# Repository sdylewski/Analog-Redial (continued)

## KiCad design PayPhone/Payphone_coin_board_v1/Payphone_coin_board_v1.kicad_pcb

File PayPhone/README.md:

# Payphone with Analog Redial

**In progress.** The Payphone tab is written and the coin board is released for fab, but
nothing here has run on a real payphone yet: no coin board has been built, and the firmware
has only run against simulated chips.

Analog Redial can run a real coin payphone: the handset lifts, a spoken message asks for
coins, the coin switches (or the line's coin tones) add up the credit, and the board
collects or returns the coins by firing the phone's coin relay. The project's first phone is
a GTE / Quadrum 120B style set.

| Doc | Covers |
|---|---|
| This one | the project as a whole: what the pieces are, status, payphone types, links |
| [coin-board.md](coin-board.md) | the coin board: how it works, output stage wiring pin by pin, parts and PCB layout |
| [payphone-firmware.md](payphone-firmware.md) | the firmware: the Payphone tab (coin tones, coin required, messages, log) and the coin board's driver |

Public version of the board reference: [docs/hardware-coin-board.md](../docs/hardware-coin-board.md).

## The pieces

- **Main board:** any Analog Redial board for the Payphone tab (coin required, messages,
  coin tones, the coin counter). The coin board plugs into v6's J11 I²C header.
- **Coin board** (`Payphone_coin_board_v1/`): makes up to 119 V to fire the coin relay in
  either direction, reads the 5 / 10 / 25 cent switches, and talks I²C. Released for fab,
  untested.
- **Instruction cards** (`instruction_cards/`): the printed cards for the phone's
  upper and lower panels, and their standard sizes (see its README).
- **Firmware** (`firmware/components/payphone/`, `coinboard/`): see
  [payphone-firmware.md](payphone-firmware.md).

## Payphone types

Payphones differ in how they report coins and how their coin relay is driven. These tables
collect what each known phone needs, one row per phone, so the firmware can later offer a
phone type to pick instead of setting each value by hand. Until then, the values in the
last table are the ones to set on the Payphone tab and on the coin board's jumpers.

To add a phone, add a row to each table, mark anything not measured **[verify]**, and note
in the last column where the numbers came from.

### 1. Identification

| Phone | Housing | Controller board | Made | Source |
|---|---|---|---|---|
| **GTE / Quadrum 120B style** (the project's first phone) | GTE / Quadrum, coin return lower right | **HB-1301-B** (40-pin DIP, two CP Clare reed relays, 310 V gas tube); smart or dumb not known **[verify]** | week 51, 1997 | photos and bench tests, 2026-10-24 to 2026-10-31 |

### 2. Coin detection

| Phone | Sensor | Cable | Wires | Signal | Coins | Coin tones |
|---|---|---|---|---|---|---|
| GTE / Quadrum 120B style | passive coin switches (measured) | 4-wire, Molex KK 396 (coin board J3) | green common; white quarter, red dime, blue nickel | contact to common, closes briefly per coin | 5, 10, 25 cents | not checked **[verify]** |

### 3. Coin relay

| Phone | Relay | Coils | Wires | Resistance | Operates at | Direction | Switch-off | Cable |
|---|---|---|---|---|---|---|---|---|
| GTE / Quadrum 120B style | **HD550002C** (QTI) | one, polarized | white and green to the coil path; red not connected | about 1 k at rest; 0.1 ohm across the coil once operated | 55 V no; **60 V yes** | white positive: lever left, **collect** (bench; confirm in the phone) **[verify]**; reversed: lever right, return | a contact on the white-green path opens as it operates, so it switches itself off | 3-wire, Molex KK 396 (coin board J2) |

### 4. Coin board settings

| Phone | Relay connector | J10 (two-coil) | HV (J14, J7-J9) | Pulse | Swap | Coin 4 | Tested |
|---|---|---|---|---|---|---|---|
| GTE / Quadrum 120B style | J2 | off | fit J14; start at 60 V (J14 + J9), up to 78 V (J14 + J8) if it doesn't move reliably | 100 ms (default); the relay cuts its own current | **on**: the plug has white on J2 pin 3, so POL high is collect; confirm with a Collect test | 0 (not fitted) | **no** |

Notes on the columns:

- **HV** is set by shunts, not by firmware: [coin-board.md](coin-board.md#part-1-design)
  Part 1, section 6 has the table. Without J14 it stays at about 19 V, for 12-24 V coils.
- **Pulse** and **Swap** are on the Payphone tab's coin board card. Swap reverses which
  way Collect and Return drive the relay.
- **Coin 4** is the cents value of the fourth coin input (0 = only logged).

### Still to find out for the first phone

- Whether the HB-1301-B board is smart (counts coins itself) or dumb (central-office
  controlled), and whether the phone sends coin tones on the line.
- Which relay direction the phone's own levers treat as collect, with the relay back in
  the phone.
- What resets the relay's latched levers.

## Other payphone projects

People keep payphones running, or put them back on a network, in many places. These are
worth reading for ideas on hardware, phone service and keeping a phone legal and cheap to
run:

- [PhilTel](https://philtel.org/about/): Philadelphia. Free calls within North America from
  refurbished payphones with coinless boards, an Asterisk server and an ATA at each site;
  its [docs are open source](https://github.com/philtelco/philtel-docs).
- [Futel](https://futel.net): Portland, Oregon.
- [Talk To Me](http://talktomenyc.com/): New York City.
- [RandTel](https://randtel.co/): central Vermont.
- [Good Phone Project](https://www.goodphoneproject.com/): Monroe County, New York.
- [0DIAL](https://0dial.net/): Canada.
- [OIRCT](https://oirct.org/): France.

(PhilTel's About page links to the others.)

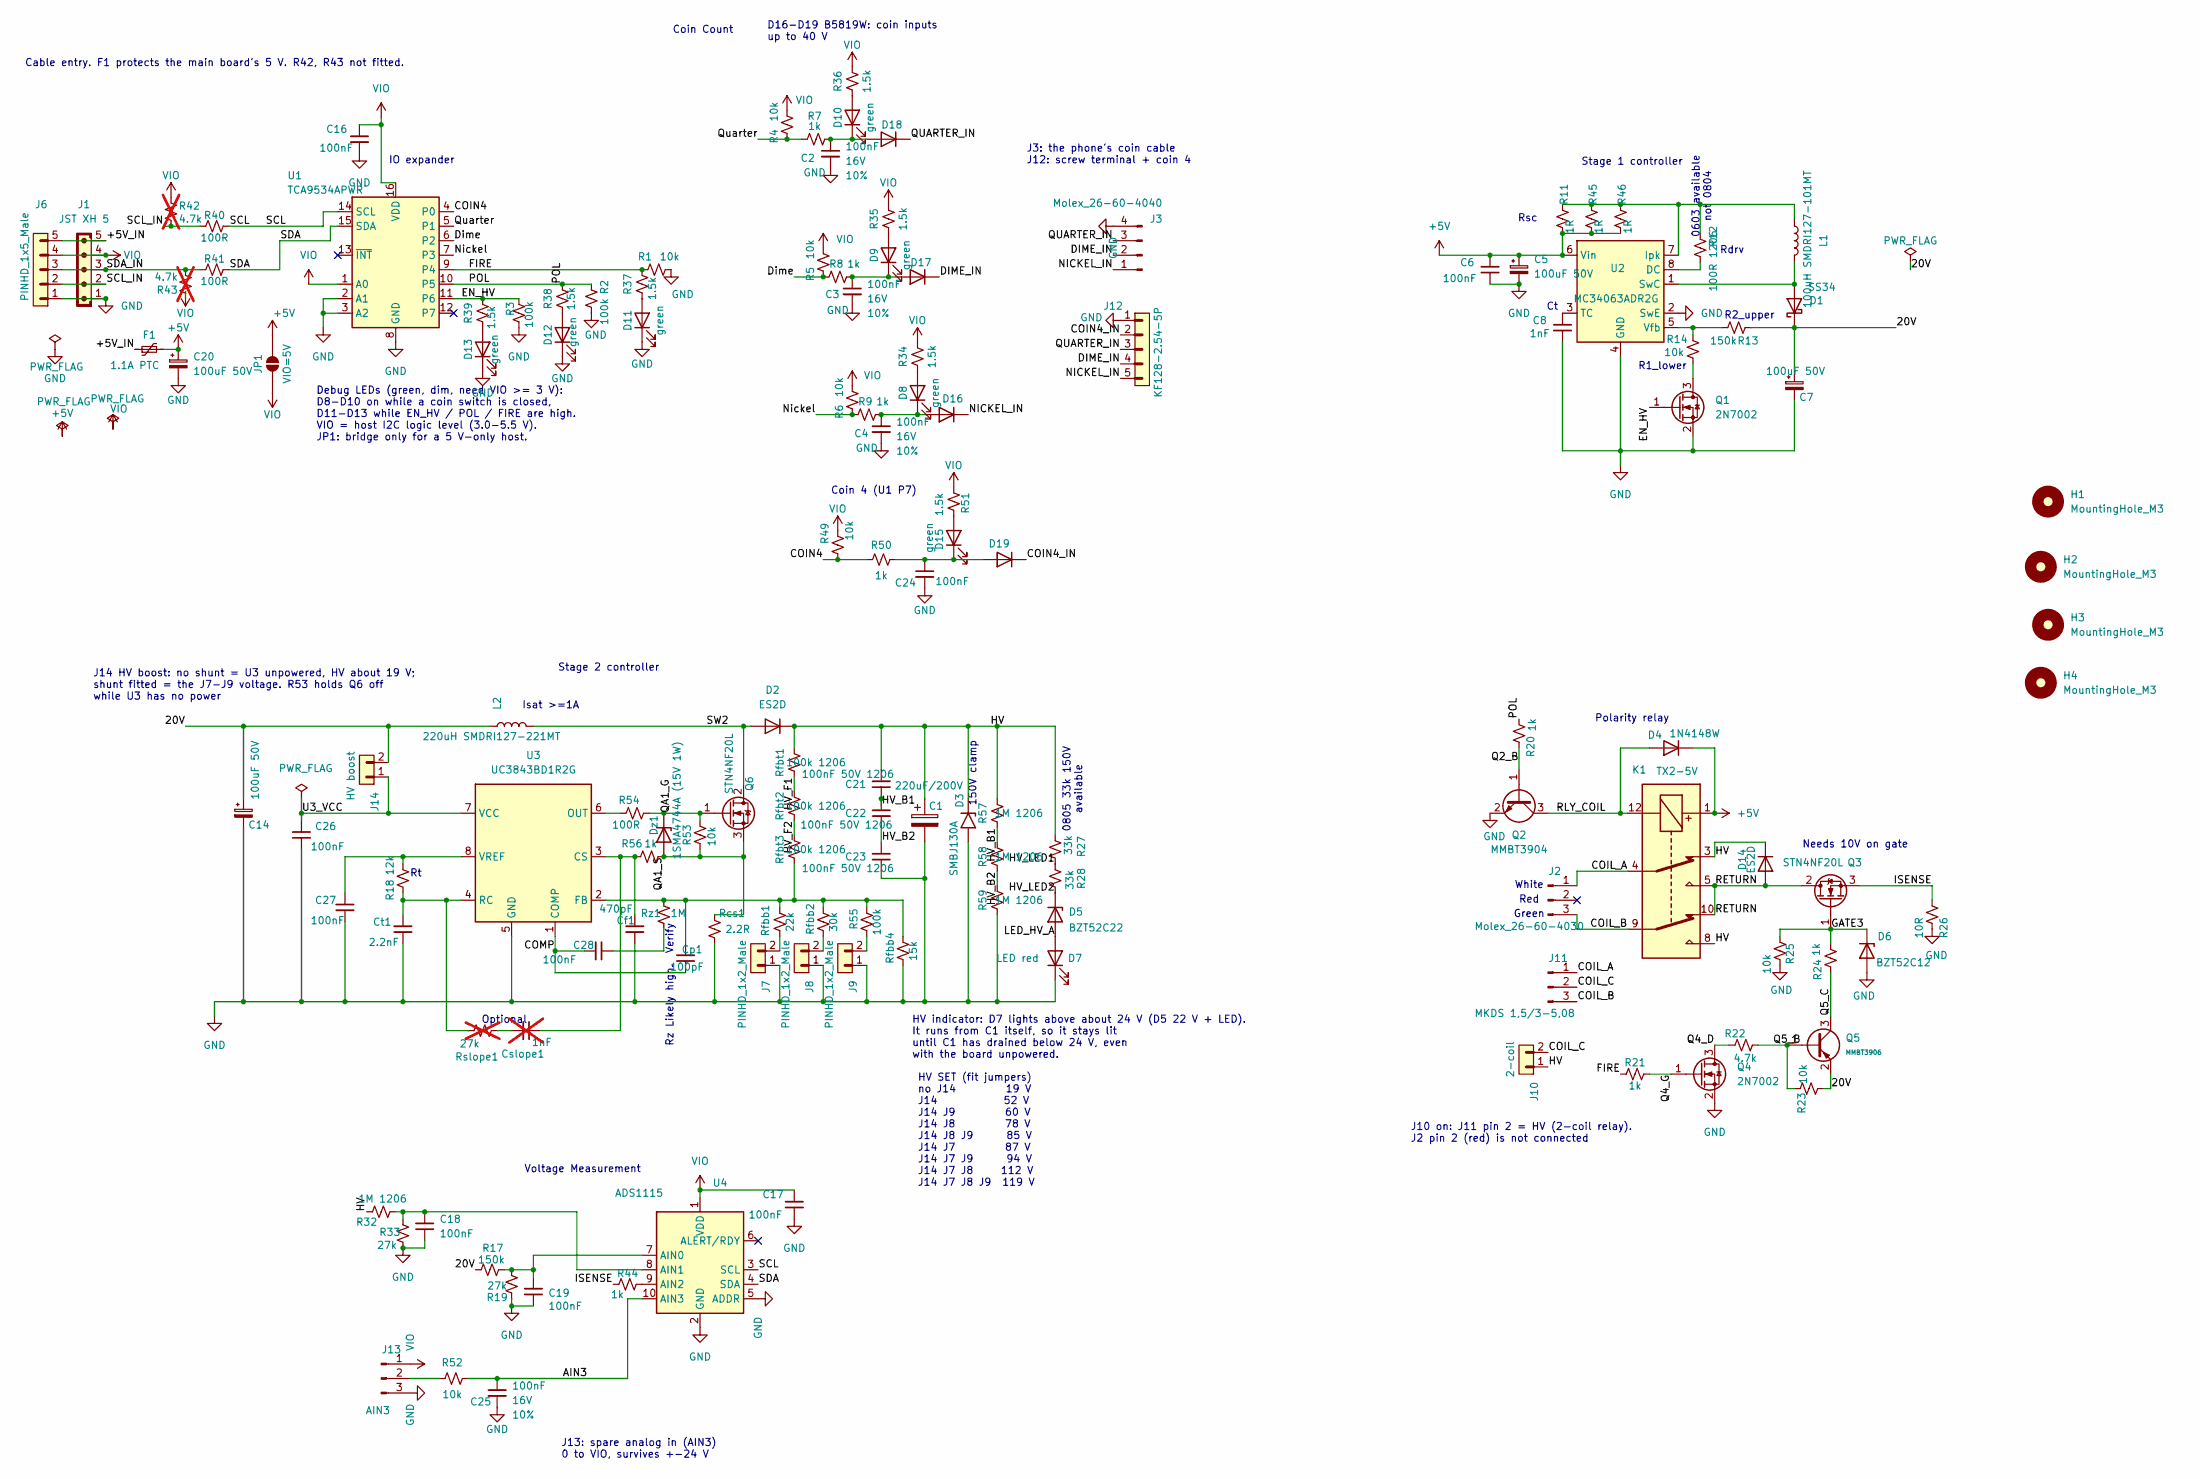
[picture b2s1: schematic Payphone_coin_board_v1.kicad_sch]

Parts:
C1: 220uF/200V; CP_Radial_D18.0mm_P7.50mm
C2, C3, C4, C24, C25: 100nF; C_0805_2012Metric; Voltage 16V; Tolerance 10%; LCSC C28233
C5, C7, C14, C20: 100uF 50V; CP_Elec_8x10
C6, C16, C17, C18, C19, C26, C27, C28: 100nF; C_0805_2012Metric; LCSC C28233
C8: 1nF; C_0805_2012Metric; LCSC C46653
C21, C22, C23: 100nF 50V 1206; C_1206_3216Metric; LCSC C24497
Cf1: 470pF; C_0805_2012Metric; LCSC C1743
Cp1: 100pF; C_0805_2012Metric; LCSC C1790
Cslope1: 1nF; C_0805_2012Metric; LCSC C46653; not fitted
Ct1: 2.2nF; C_0805_2012Metric; LCSC C28260
D1: SS34; D_SMA; LCSC C8678
D2, D14: ES2D; D_SMA; LCSC C18199161
D3: SMBJ130A; D_SMB
D4: 1N4148W; D_SOD-123; LCSC C81598
D5: BZT52C22; D_SOD-123; LCSC C22375295
D6: BZT52C12; D_SOD-123; LCSC C19077410
D7: LED red; LED_0805_2012Metric; LCSC C84256
D8, D9, D10, D11, D12, D13, D15: green; LED_0805_2012Metric; LCSC C2297
D16, D17, D18, D19: B5819W; D_SOD-123; LCSC C8598
Dz1: 1SMA4744A (15V 1W); D_SMA; LCSC C19077482
F1: 1.1A PTC; Fuse_1812_4532Metric
H1, H2, H3, H4: MountingHole_M3; MountingHole_3.2mm_M3
J1: JST XH 5; JST_XH_B5B-XH-A_1x05_P2.50mm_Vertical
J2: Molex_26-60-4030; Molex_KK-396_A-41791-0003_1x03_P3.96mm_Vertical; MPN 0026604030; DigiKey WM4621-ND
J3: Molex_26-60-4040; Molex_KK-396_A-41791-0004_1x04_P3.96mm_Vertical; MPN 0026604040; DigiKey WM4622-ND
J6: PINHD_1x5_Male; PinHeader_1x05_P2.54mm_Vertical
J7, J8, J9: PINHD_1x2_Male; PinHeader_1x02_P2.54mm_Vertical
J10: 2-coil; PinHeader_1x02_P2.54mm_Vertical
J11: MKDS 1,5/3-5,08; TerminalBlock_Phoenix_MKDS-1,5-3-5.08_1x03_P5.08mm_Horizont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
J12: KF128-2.54-5P; TerminalBlock_Xinya_XY308-2.54-5P_1x05_P2.54mm_Horizontal
J13: AIN3; PinHeader_1x03_P2.54mm_Vertical
J14: HV boost; PinHeader_1x02_P2.54mm_Vertical
JP1: VIO=5V; SolderJumper-2_P1.3mm_Open_RoundedPad1.0x1.5mm
K1: TX2-5V; Relay_DPDT_Omron_G6S-2
L1: 100uH SMDRI127-101MT; L_SXN_SMDRI127; LCSC C10150
L2: 220uH SMDRI127-221MT; L_SXN_SMDRI127; LCSC C10151
Q1, Q4: 2N7002; SOT-23; LCSC C8545
Q2: MMBT3904; SOT-23; LCSC C20526
Q3, Q6: STN4NF20L; SOT-223-3_TabPin2; LCSC C7603336
Q5: MMBT3906; SOT-23; Part MMBT3906; LCSC C7420354
R1, R4, R5, R6, R14, R23, R25, R49, R52, R53: 10k; R_0805_2012Metric; LCSC C17414
R2, R3, R55: 100k; R_0805_2012Metric; LCSC C149504
R7, R8, R9, R20, R21, R24, R44, R50, R56: 1k; R_0805_2012Metric; LCSC C17513
R11, R45, R46: 1R; R_1206_3216Metric; LCSC C17928
R12: 100R 1206; R_1206_3216Metric; LCSC C17901
R13, R17: 150k; R_0805_2012Metric; LCSC C17470
R18: 12k; R_0805_2012Metric; LCSC C17444
R19, R33: 27k; R_0805_2012Metric; LCSC C17593
R22: 4.7k; R_0805_2012Metric; LCSC C17673
R26: 10R; R_1206_3216Metric; LCSC C17903
R27, R28: 33k; R_0805_2012Metric_Pad1.20x1.40mm_HandSolder; LCSC C17633
R32, R57, R58, R59: 1M 1206; R_1206_3216Metric; LCSC C17927
R34, R35, R36, R37, R38, R39, R51: 1.5k; R_0805_2012Metric; LCSC C4310
R40, R41, R54: 100R; R_0805_2012Metric; LCSC C17408
R42, R43: 4.7k; R_0805_2012Metric; LCSC C17673; not fitted
Rcs1: 2.2R; R_0805_2012Metric; LCSC C17521
Rfbb1: 22k; R_0805_2012Metric; LCSC C17560
Rfbb2: 30k; R_0805_2012Metric; LCSC C17621
Rfbb4: 15k; R_0805_2012Metric; LCSC C17475
Rfbt1, Rfbt2, Rfbt3: 100k 1206; R_1206_3216Metric; LCSC C17900
Rslope1: 27k; R_0805_2012Metric; LCSC C17593; not fitted
Rz1: 1M; R_0805_2012Metric; LCSC C17514
U1: TCA9534APWR; TSSOP-16_4.4x5mm_P0.65mm; LCSC C206010
U2: MC34063ADR2G; SOIC-8_3.9x4.9mm_P1.27mm; LCSC C32078
U3: UC3843BD1R2G; SOIC-8_3.9x4.9mm_P1.27mm
U4: ADS1115; ADS1115 Module

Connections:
+5V: C5.1, C6.2, C20.1, D4.1 (K), F1.2, JP1.2 (B), K1.1, R11.2, R45.2, R46.2, U2.6 (Vin)
/20V: C7.1, C14.1, D1.1 (K), J14.2, L2.1, Q5.2 (E), R13.2, R17.2, R23.1
/+5V_IN: F1.1, J1.5, J6.5
/AIN3: C25.1, R52.1, U4.10 (AIN3)
/COIL_A: J2.1, J11.1, K1.4
/COIL_B: J2.3, J11.3, K1.9
/COIL_C: J10.2, J11.2
/COIN4: R49.1, R50.2, U1.4 (P0)
/COIN4_IN: D19.1 (K), J12.2
/COMP: C28.1, Cp1.1, U3.1 (COMP)
/DIME_IN: D17.1 (K), J3.2, J12.4
/Dime: R5.2, R8.2, U1.6 (P2)
/EN_HV: Q1.1 (G), R3.1, R39.2, U1.11 (P6)
/FIRE: R1.2, R21.1, R37.2, U1.9 (P4)
/GATE3: D6.1 (K), Q3.1 (G), R24.2, R25.1
/HV: C1.1, C21.1, D2.1 (K), D3.1 (A1), D14.1 (K), J10.1, K1.3, K1.8, R27.2, R32.2, R57.2, Rfbt1.2
/HV_B1: C21.2, C22.1, R57.1, R58.2
/HV_B2: C22.2, C23.1, R58.1, R59.2
/HV_F1: Rfbt1.1, Rfbt2.2
/HV_F2: Rfbt2.1, Rfbt3.2
/HV_LED1: R27.1, R28.2
/HV_LED2: D5.1 (K), R28.1
/ISENSE: Q3.3 (S), R26.1, R44.1
/LED_HV_A: D5.2 (A), D7.2 (A)
/NICKEL_IN: D16.1 (K), J3.1, J12.5
/Nickel: R6.2, R9.2, U1.7 (P3)
/POL: R2.2, R20.1, R38.2, U1.10 (P5)
/Q2_B: Q2.1 (B), R20.2
/Q4_D: Q4.3 (D), R22.1
/Q4_G: Q4.1 (G), R21.2
/Q5_B: Q5.1 (B), R22.2, R23.2
/Q5_C: Q5.3 (C), R24.1
/QA1_G: Dz1.1 (K), Q6.1 (G), R53.2, R54.1
/QA1_S: Dz1.2 (A), Q6.3 (S), R53.1, R56.1, Rcs1.2
/QUARTER_IN: D18.1 (K), J3.3, J12.3
/Quarter: R4.2, R7.2, U1.5 (P1)
/RETURN: D14.2 (A), K1.5, K1.10, Q3.2 (D)
/RLY_COIL: D4.2 (A), K1.12, Q2.3 (C)
/SCL: R40.2, U1.14 (SCL), U4.3 (SCL)
/SCL_IN: J1.2, J6.2, R40.1, R42.1
/SDA: R41.2, U1.15 (SDA), U4.4 (SDA)
/SDA_IN: J1.3, J6.3, R41.1, R43.1
/SW2: D2.2 (A), L2.2, Q6.2 (D)
/U3_VCC: C26.2, J14.1, U3.7 (VCC)
GND: C1.2, C2.2, C3.2, C4.2, C5.2, C6.1, C7.2, C8.1, C14.2, C16.2, C17.2, C18.2, C19.2, C20.2, C23.2, C24.2, C25.2, C26.1, C27.1, Cf1.1, Ct1.1, D3.2 (A2), D6.2 (A), D7.1 (K), D11.1 (K), D12.1 (K), D13.1 (K), J1.1, J3.4, J6.1, J7.1, J8.1, J9.1, J12.1, J13.3, Q1.2 (S), Q2.2 (E), Q4.2 (S), R1.1, R2.1, R3.2, R19.1, R25.2, R26.2, R33.1, R59.1, Rcs1.1, Rfbb4.1, U1.2 (A1), U1.3 (A2), U1.8 (GND), U2.2 (SwE), U2.4 (GND), U3.5 (GND), U4.2 (GND), U4.5 (ADDR)
unnamed: C28.2, Rz1.1
unnamed: Cslope1.2, Rslope1.2
unnamed: D1.2 (A), L1.2, U2.1 (SwC)
unnamed: D8.2 (A), R34.1
unnamed: D9.2 (A), R35.1
unnamed: D10.2 (A), R36.1
unnamed: C2.1, D10.1 (K), D18.2 (A), R7.1
unnamed: D11.2 (A), R37.1
unnamed: D12.2 (A), R38.1
unnamed: D13.2 (A), R39.1
unnamed: D15.2 (A), R51.1
unnamed: C24.1, D15.1 (K), D19.2 (A), R50.1
unnamed: C4.1, D8.1 (K), D16.2 (A), R9.1
unnamed: C3.1, D9.1 (K), D17.2 (A), R8.1
unnamed: J7.2, Rfbb1.1
unnamed: J8.2, Rfbb2.1
unnamed: J9.2, R55.1
unnamed: J13.2, R52.2
unnamed: Q1.3 (D), R14.2
unnamed: R12.1, U2.8 (DC)
unnamed: L1.1, R11.1, R12.2, R45.1, R46.1, U2.7 (Ipk)
unnamed: C8.2, U2.3 (TC)
unnamed: R13.1, R14.1, U2.5 (Vfb)
unnamed: Cf1.2, Cslope1.1, R56.2, U3.3 (CS)
unnamed: Cp1.2, R55.2, Rfbb1.2, Rfbb2.2, Rfbb4.2, Rfbt3.1, Rz1.2, U3.2 (FB)
unnamed: R54.2, U3.6 (OUT)
unnamed: Ct1.2, R18.2, Rslope1.1, U3.4 (RC)
unnamed: C27.2, R18.1, U3.8 (VREF)
unnamed: C19.1, R17.1, R19.2, U4.7 (AIN0)
unnamed: C18.1, R32.1, R33.2, U4.8 (AIN1)
unnamed: R44.2, U4.9 (AIN2)
VIO: C16.1, C17.1, J1.4, J6.4, J13.1, JP1.1 (A), R4.1, R5.1, R6.1, R34.2, R35.2, R36.2, R42.2, R43.2, R49.2, R51.2, U1.1 (A0), U1.16 (VDD), U4.1 (VDD)

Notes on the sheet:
Voltage Measurement
Rdrv
J14 HV boost: no shunt = U3 unpowered, HV about 19 V; shunt fitted = the J7-J9 voltage. R53 holds Q6 off while U3 has no power
D16-D19 B5819W: coin inputs up to 40 V
R2_upper
Debug LEDs (green, dim, need VIO >= 3 V): D8-D10 on while a coin switch is closed, D11-D13 while EN_HV / POL / FIRE are high. VIO = host I2C logic level (3.0-5.5 V). JP1: bridge only for a 5 V-only host.
Coin Count
IO expander
Needs 10V on gate
Cable entry. F1 protects the main board's 5 V. R42, R43 not fitted.
0805 33k 150V available
Stage 1 controller
Rz Likely high. Verify
Isat >=1A
Coin 4 (U1 P7)
White
Rsc
Optional
Green
150V clamp
HV SET (fit jumpers) no J14 19 V J14 52 V J14 J9 60 V J14 J8 78 V J14 J8 J9 85 V J14 J7 87 V J14 J7 J9 94 V J14 J7 J8 112 V J14 J7 J8 J9 119 V
HV indicator: D7 lights above about 24 V (D5 22 V + LED). It runs from C1 itself, so it stays lit until C1 has drained below 24 V, even with the board unpowered.
J10 on: J11 pin 2 = HV (2-coil relay). J2 pin 2 (red) is not connected
Red
Polarity relay
0603 available not 0804
R1_lower
Stage 2 controller
J13: spare analog in (AIN3) 0 to VIO, survives +-24 V
J3: the phone's coin cable J12: screw terminal + coin 4

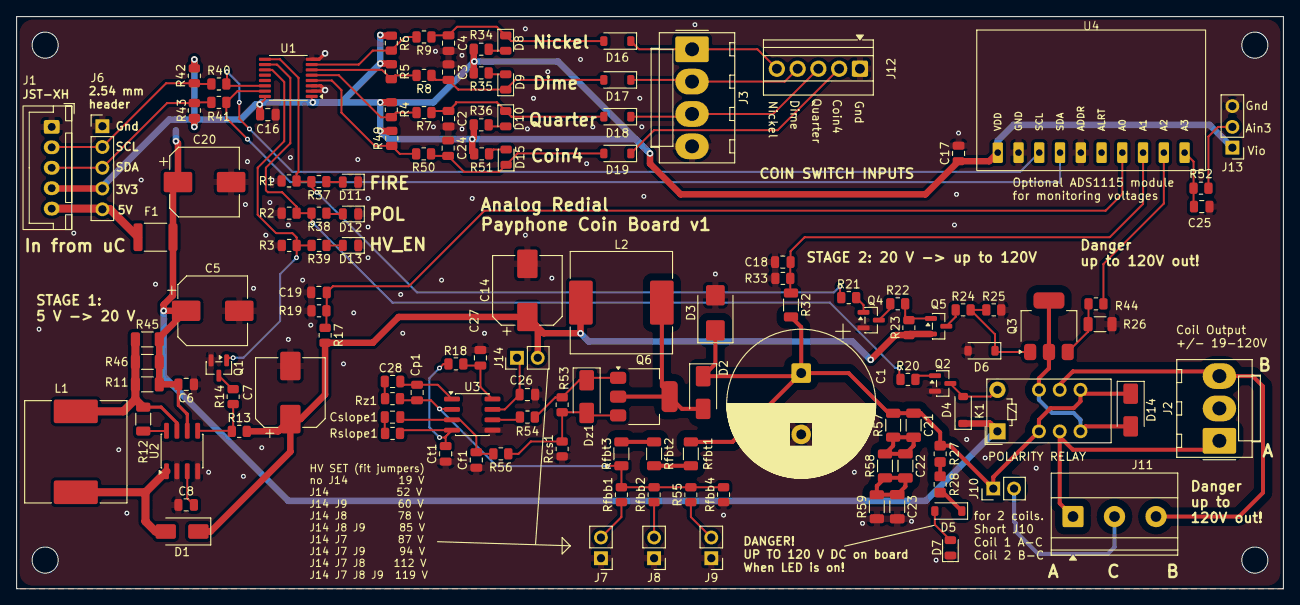
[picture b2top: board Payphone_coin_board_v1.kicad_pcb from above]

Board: 2 copper layers, 155.0 x 70.0 mm, 137 parts (1 on the bottom side), 77 nets.

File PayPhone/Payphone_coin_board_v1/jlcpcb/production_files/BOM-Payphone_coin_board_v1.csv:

Comment,Designator,Footprint,LCSC,Quantity
1.5k,"R34,R35,R36,R37,R38,R39,R51",R_0805_2012Metric,C4310,7
100R,"R40,R41,R54",R_0805_2012Metric,C17408,3
100R 1206,R12,R_1206_3216Metric,C17901,1
100k,"R2,R3,R55",R_0805_2012Metric,C149504,3
100k 1206,"Rfbt1,Rfbt2,Rfbt3",R_1206_3216Metric,C17900,3
100nF,"C16,C17,C18,C19,C2,C24,C25,C26,C27,C28,C3,C4,C6",C_0805_2012Metric,C28233,13
100nF 50V 1206,"C21,C22,C23",C_1206_3216Metric,C24497,3
100pF,Cp1,C_0805_2012Metric,C1790,1
100uH SMDRI127-101MT,L1,L_SXN_SMDRI127,C10150,1
10R,R26,R_1206_3216Metric,C17903,1
10k,"R1,R14,R23,R25,R4,R49,R5,R52,R53,R6",R_0805_2012Metric,C17414,10
12k,R18,R_0805_2012Metric,C17444,1
150k,"R13,R17",R_0805_2012Metric,C17470,2
15k,Rfbb4,R_0805_2012Metric,C17475,1
1M,Rz1,R_0805_2012Metric,C17514,1
1M 1206,"R32,R57,R58,R59",R_1206_3216Metric,C17927,4
1N4148W,D4,D_SOD-123,C81598,1
1R,"R11,R45,R46",R_1206_3216Metric,C17928,3
1SMA4744A (15V 1W),Dz1,D_SMA,C19077482,1
1k,"R20,R21,R24,R44,R50,R56,R7,R8,R9",R_0805_2012Metric,C17513,9
1nF,C8,C_0805_2012Metric,C46653,1
2.2R,Rcs1,R_0805_2012Metric,C17521,1
2.2nF,Ct1,C_0805_2012Metric,C28260,1
220uH SMDRI127-221MT,L2,L_SXN_SMDRI127,C10151,1
22k,Rfbb1,R_0805_2012Metric,C17560,1
27k,"R19,R33",R_0805_2012Metric,C17593,2
2N7002,"Q1,Q4",SOT-23,C8545,2
30k,Rfbb2,R_0805_2012Metric,C17621,1
33k,"R27,R28",R_0805_2012Metric_Pad1.20x1.40mm_HandSolder,C17633,2
4.7k,R22,R_0805_2012Metric,C17673,1
470pF,Cf1,C_0805_2012Metric,C1743,1
B5819W,"D16,D17,D18,D19",D_SOD-123,C8598,4
BZT52C12,D6,D_SOD-123,C19077410,1
BZT52C22,D5,D_SOD-123,C22375295,1
ES2D,"D14,D2",D_SMA,C18199161,2
LED red,D7,LED_0805_2012Metric,C84256,1
MC34063ADR2G,U2,SOIC-8_3.9x4.9mm_P1.27mm,C32078,1
MMBT3904,Q2,SOT-23,C20526,1
MMBT3906,Q5,SOT-23,C7420354,1
SS34,D1,D_SMA,C8678,1
STN4NF20L,"Q3,Q6",SOT-223-3_TabPin2,C7603336,2
TCA9534APWR,U1,TSSOP-16_4.4x5mm_P0.65mm,C206010,1
green,"D10,D11,D12,D13,D15,D8,D9",LED_0805_2012Metric,C2297,7

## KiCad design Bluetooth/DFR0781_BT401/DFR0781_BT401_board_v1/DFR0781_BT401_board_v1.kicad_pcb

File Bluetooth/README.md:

# Bluetooth modules for the J2 header

What has been tried for the hands-free "rotary phone as a cell-phone handset" option. Newest information first.

| Module | Price | Status |
|---|---|---|
| **Microchip BM64** (carrier board in `BM64/`) | about $14 | **Works and is supported.** UART link, pairing mode and the audio EEPROM setup verified (2026-10-20); call audio and real phone pairing still to test with a handset. Supply 3.2-4.2 V on `BAT_IN`, so it needs the LDO. |
| **DFRobot DFR0781** (BT401 module, `DFR0781_BT401/`) | about $3.50 | **Works, and now the preferred option** (2026-10-27, hand-wired to a v5 board): pairing, music, ringing, dial-out and call audio, with little call delay. Text command set with call control (answer, hang up, reject, dial, caller number); no EEPROM setup step. Adapter board `DFR0781_BT401/DFR0781_BT401_board_v1/` (plugs into J2 like the BM64 carrier; Gerbers via KiCad's JLCPCB/PCBWay export): designed, not yet built or tested. Pin table in `DFR0781_BT401/BT401_NOTES.md`, firmware and bench log in `../archive/hardware/bt401.md`. |
| Microchip BM83 | about $12.20 | Candidate only. Digikey lists BM83SM1-00AA, -00AB and -00TA (read the Microchip ordering table before buying). Same 0xAA binary framing as the BM64 per Microchip's UART command documentation, so the driver would probably adapt, but footprint and pinout are not confirmed to match; needs its own carrier. Not worth the $1.80 saving unless the BM64 becomes hard to get. |
| **BK3266 / "BH519"** (`BK3266_do_not_use/`, `BK3266_board_v1` KiCad project) | about $3 | **Not working as intended.** The module powers on and pairs with a phone as an audio device ("BH519"), but its UART never answers (binary or text, 1200-460800 baud, TX/RX both ways), so the firmware cannot control calls. Notes and bench log: `BK3266_do_not_use/BK3266_RESEARCH.md` and `../archive/hardware/bk3266.md`. Kept for reference only; its firmware driver was removed (last in `v1.0.1`). |

Firmware lives in `firmware/components/bt_companion/` (the BM64 and BT401 drivers). The public docs describe the BM64 and mention the BT401 as the cheaper option.

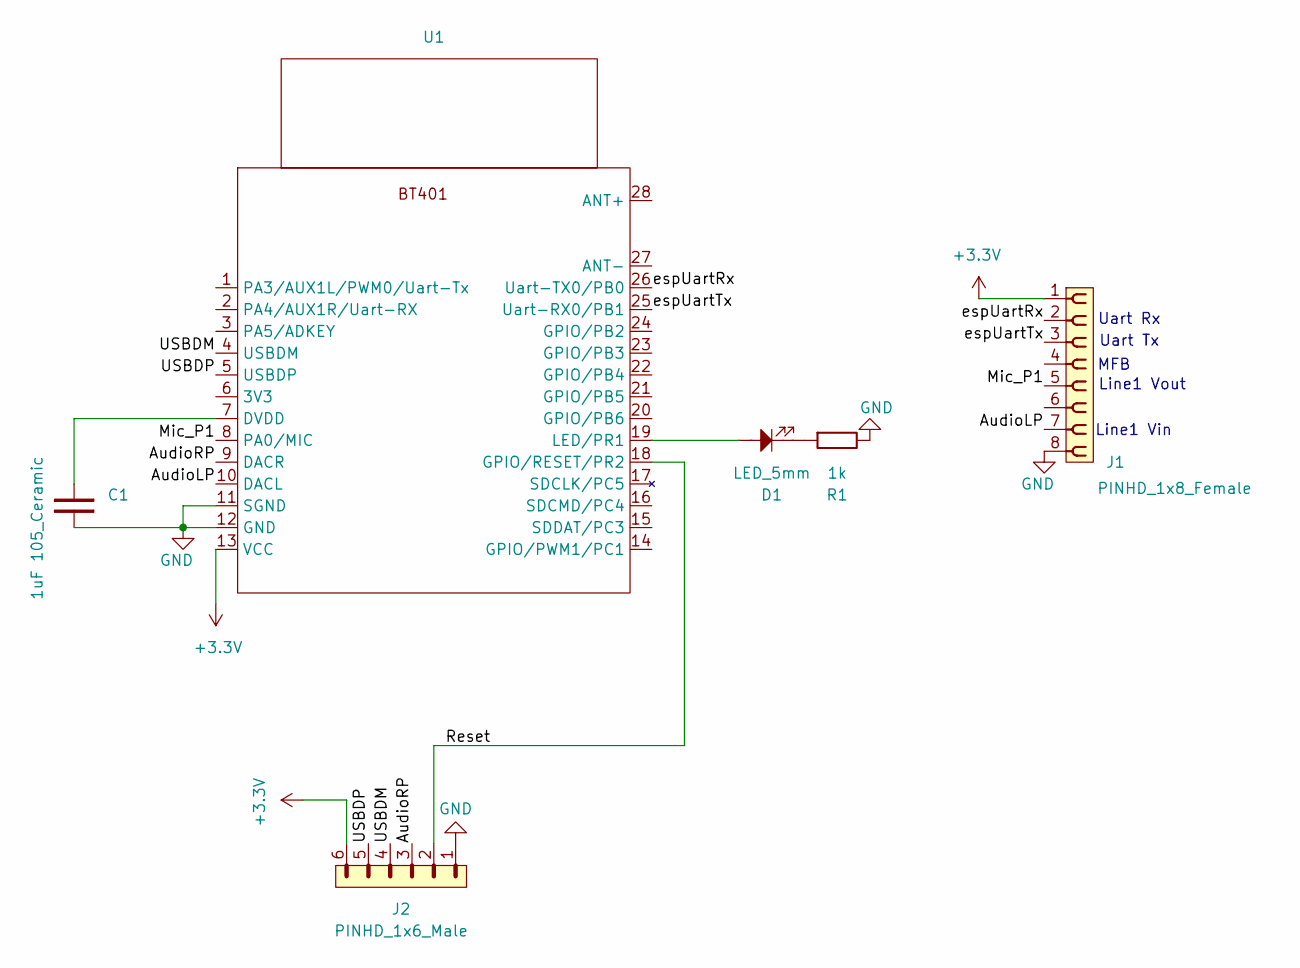
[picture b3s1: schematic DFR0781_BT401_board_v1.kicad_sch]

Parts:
C1: 1uF 105_Ceramic; C_Disc_D5.0mm_W2.5mm_P2.50mm
D1: LED_5mm; LED_D5.0mm
J1: PINHD_1x8_Female; PinSocket_1x08_P2.54mm_Vertical
J2: PINHD_1x6_Male; PinHeader_1x06_P2.54mm_Vertical
R1: 1k; R_Axial_DIN0207_L6.3mm_D2.5mm_P10.16mm_Horizontal
U1: DFR0781_BT401_new

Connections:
+3.3V: J1.1, J2.6, U1.13 (VCC)
/AudioLP: J1.7, U1.10 (DACL)
/AudioRP: J2.3, U1.9 (DACR)
/Mic_P1: J1.5, U1.8 (PA0/MIC)
/Reset: J2.2, U1.18 (GPIO/RESET/PR2)
/USBDM: J2.4, U1.4 (USBDM)
/USBDP: J2.5, U1.5 (USBDP)
/espUartRx: J1.2, U1.26 (Uart-TX0/PB0)
/espUartTx: J1.3, U1.25 (Uart-RX0/PB1)
GND: C1.2, J1.8, J2.1, R1.2, U1.11 (SGND), U1.12 (GND)
unnamed: D1.1, R1.1
unnamed: C1.1, U1.7 (DVDD)
unnamed: D1.2, U1.19 (LED/PR1)

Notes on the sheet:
Uart Tx
Line1 Vin
Uart Rx
Line1 Vout
MFB

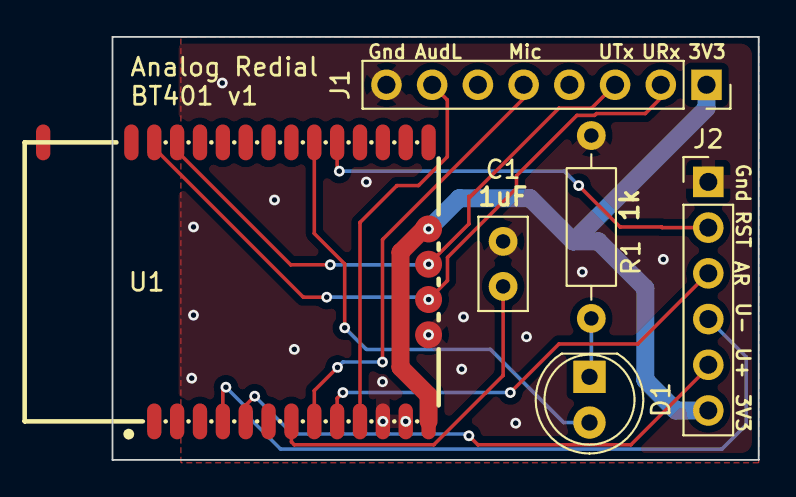
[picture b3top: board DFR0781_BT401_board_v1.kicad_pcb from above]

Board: 2 copper layers, 35.9 x 23.5 mm, 6 parts (0 on the bottom side), 13 nets.

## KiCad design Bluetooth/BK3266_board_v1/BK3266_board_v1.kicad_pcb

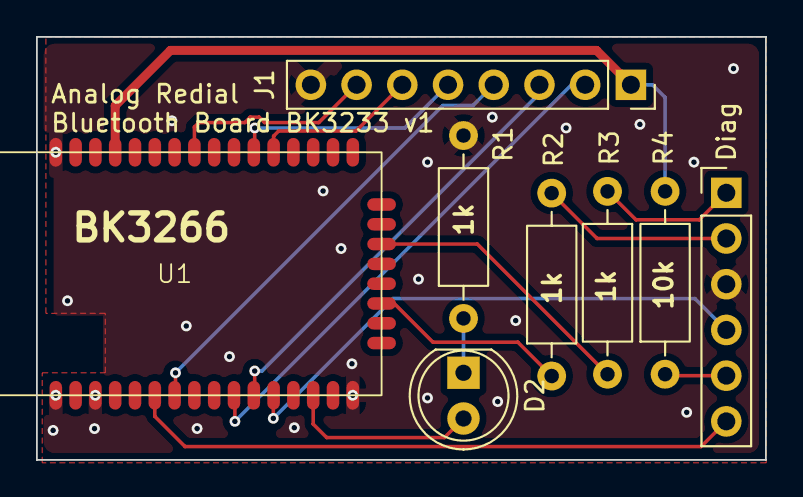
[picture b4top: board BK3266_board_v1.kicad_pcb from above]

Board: 2 copper layers, 40.5 x 23.5 mm, 8 parts (0 on the bottom side), 17 nets.

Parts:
D2: LED_5mm; LED_D5.0mm
Diag: PINHD_1x6_Male; PinHeader_1x06_P2.54mm_Vertical
J1: PINHD_1x8_Female; PinSocket_1x08_P2.54mm_Vertical
R1, R2, R3: 1k; R_Axial_DIN0207_L6.3mm_D2.5mm_P10.16mm_Horizontal
R4: 10k; R_Axial_DIN0207_L6.3mm_D2.5mm_P10.16mm_Horizontal
U1: BK3266SR

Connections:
+3.3V: J1.1, R4.2, U1.37 (VBAT_(3.3-4.2V))
/AudioLP: J1.7, U1.33 (AudioLP)
/Mic_N1: J1.6, U1.29 (MicN)
/Mic_P1: J1.5, U1.30 (MicP)
/PP_Call: Diag.6, U1.6 (P.P/Call_(GPIO4))
/Wake: J1.4, U1.7 (Wakeup_(GPIO15))
/espUartRx: J1.2, U1.10 (TX_(GPIO0))
/espUartTx: J1.3, U1.11 (RX_(GPIO1))
GND: Diag.3, J1.8, R1.2, U1.1 (GND), U1.3 (GND), U1.16 (GND), U1.40 (AGND)
unnamed: D2.1, R1.1
unnamed: Diag.1, R3.1
unnamed: Diag.2, R2.2
unnamed: Diag.5, R4.1
unnamed: D2.2, U1.14 (LED_(GPIO8))
unnamed: Diag.4, U1.12 (Mode_(GPIO7)#1)
unnamed: R2.1, U1.19 (STAT_(GPIO10_)
unnamed: R3.2, U1.22 (S/R_(GPIO6)#2)

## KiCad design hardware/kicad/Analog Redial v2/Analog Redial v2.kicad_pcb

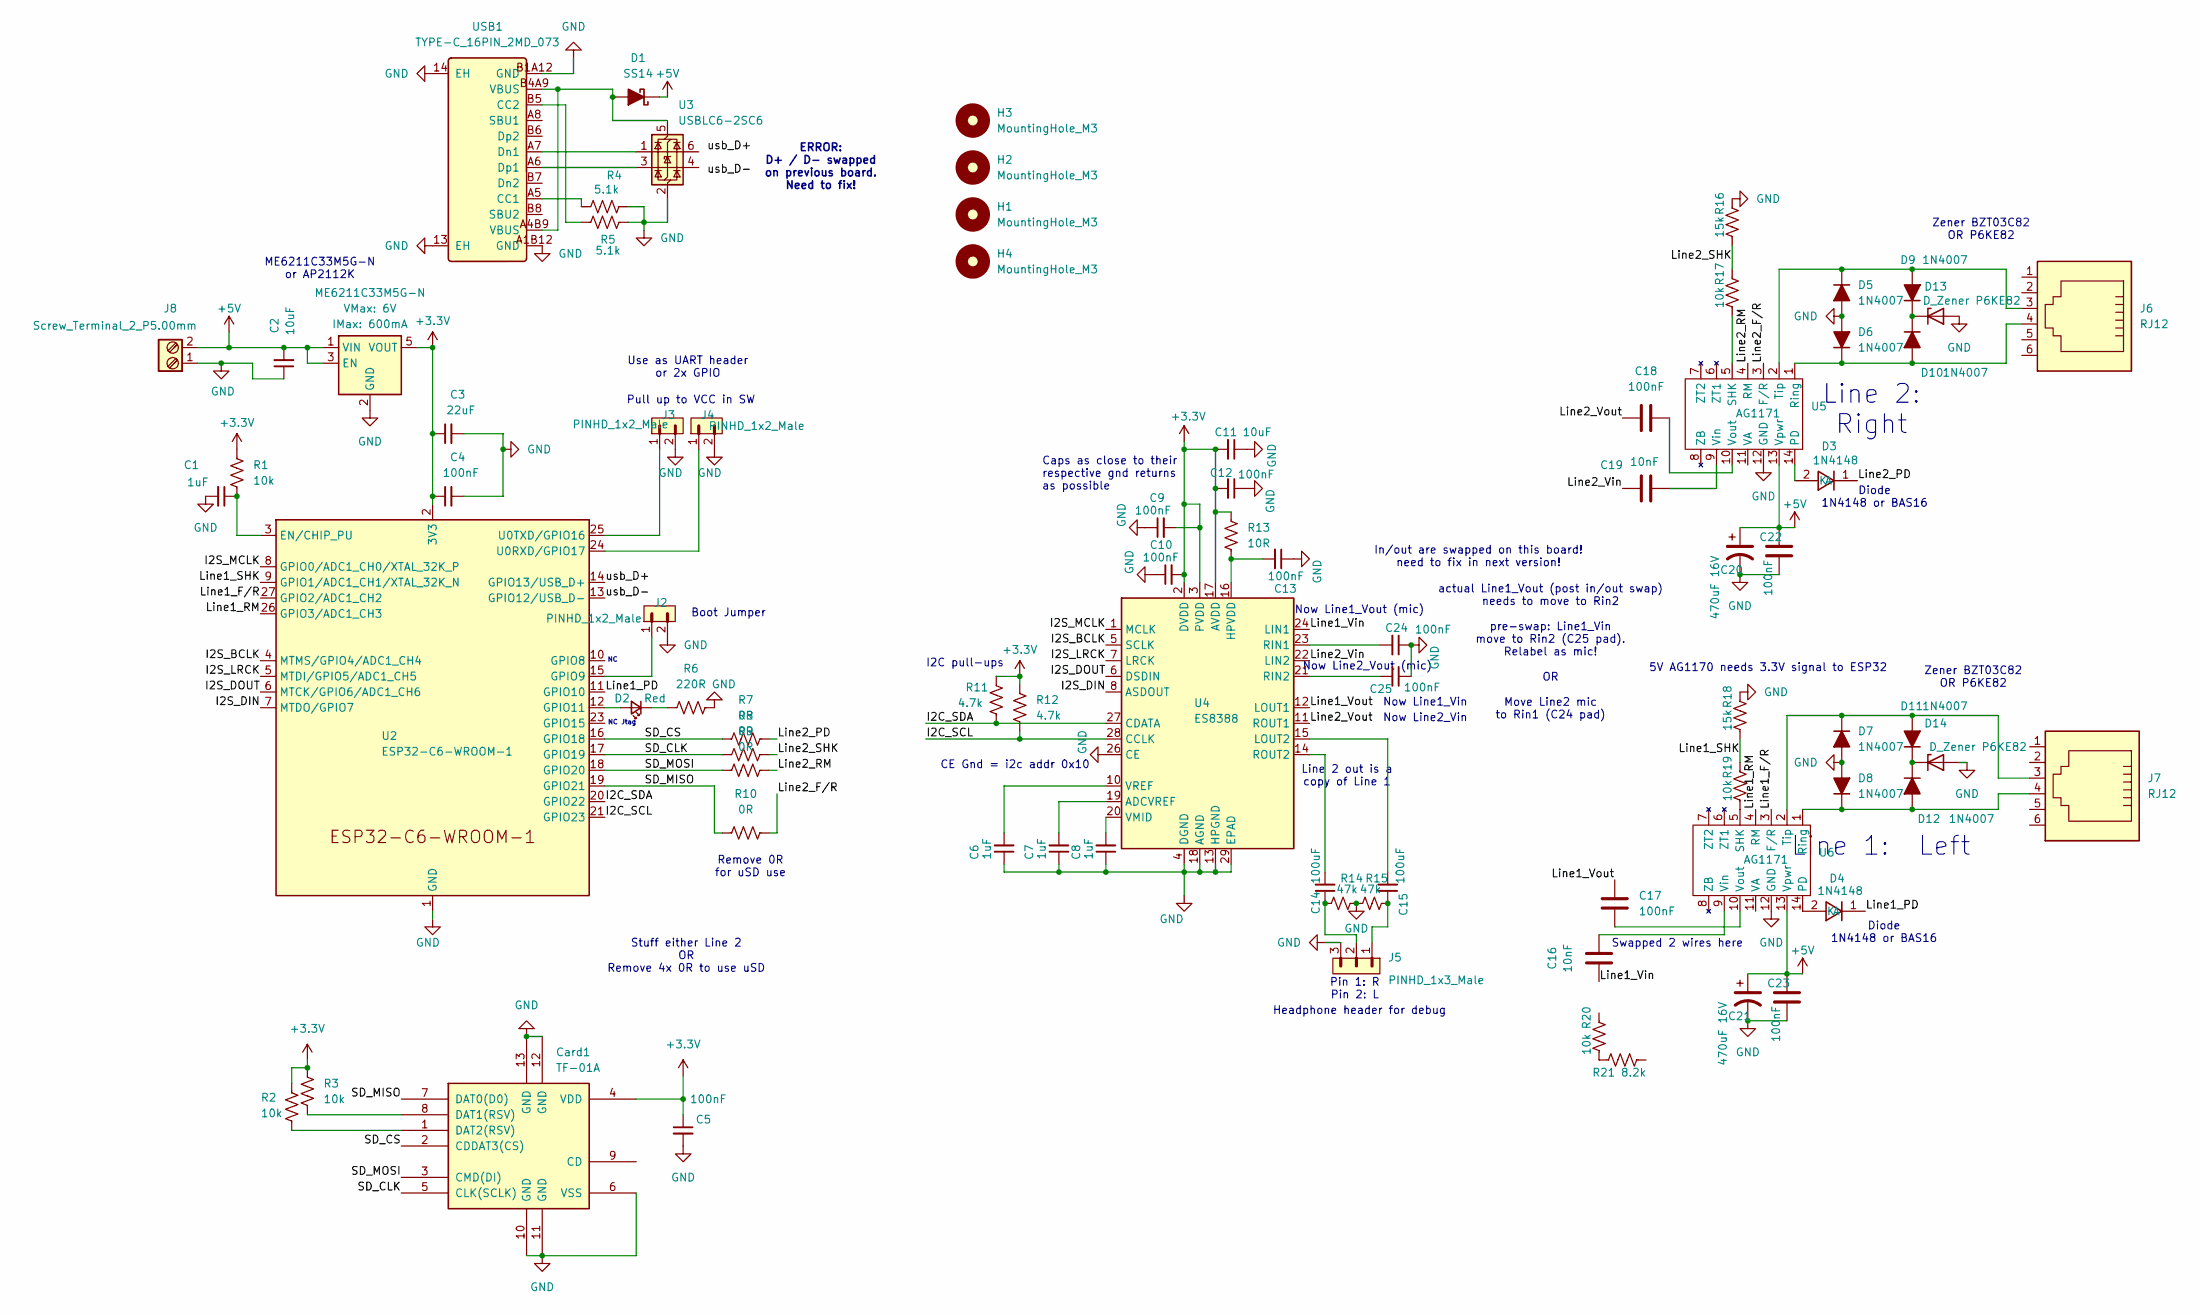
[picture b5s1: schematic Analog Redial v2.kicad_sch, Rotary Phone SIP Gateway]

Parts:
C1, C6, C7, C8: 1uF; C_0402_1005Metric; Voltage 1kV; Tolerance 100%
C2, C11: 10uF; C_0402_1005Metric; Voltage 1kV; Tolerance 100%
C3: 22uF; C_0603_1608Metric; Voltage 1kV; Tolerance 100%
C4, C5, C9, C10, C12, C13, C24, C25: 100nF; C_0402_1005Metric; Voltage 1kV; Tolerance 100%
C14, C15: 100uF; C_1206_3216Metric; Voltage 1kV; Tolerance 100%
C16, C19: 10nF; C_0402_1005Metric
C17, C18, C22, C23: 100nF; C_0402_1005Metric
C20, C21: 470uF 16V; CP_Radial_D6.3mm_P2.50mm
Card1: TF-01A; Manufacturer Part TF-01A; LCSC C91145
D1: SS14; D_SMA
D2: Red; LED_0603_1608Metric_Red
D3, D4: 1N4148; 1N4148W_C81598; Manufacturer Part 1N4148W; LCSC C81598
D5, D6, D7, D8, D9, D10, D11, D12: 1N4007; 1N4007W_C18199088
D13, D14: D_Zener P6KE82; D_DO-41_SOD81_P10.16mm_Horizontal
H1, H2, H3, H4: MountingHole_M3; MountingHole_3.2mm_M3
J2, J3, J4: PINHD_1x2_Male; PinHeader_1x02_P2.54mm_Vertical
J5: PINHD_1x3_Male; PinHeader_1x03_P2.54mm_Vertical
J6, J7: RJ12; RJ12_Amphenol_87180_Horizontal
J8: Screw_Terminal_2_P5.00mm; TerminalBlock_Phoenix_PT-1,5-2-5.0-H_1x02_P5.00mm_Horizontal
R1, R2, R3, R17, R19, R20: 10k; R_0402_1005Metric
R4, R5: 5.1k; R_0402_1005Metric
R6: 220R; R_0402_1005Metric
R7, R8, R9, R10: 0R; R_0402_1005Metric
R11, R12: 4.7k; R_0402_1005Metric
R13: 10R; R_0402_1005Metric
R14, R15: 47k; R_0402_1005Metric
R16, R18: 15k; R_0402_1005Metric
R21: 8.2k; R_0402_1005Metric
U1: ME6211C33M5G-N; SOT23-5
U2: ESP32-C6-WROOM-1
U3: USBLC6-2SC6; SOT-23-6
U4: ES8388; QFN-28-1EP_4x4mm_P0.45mm_EP2.6x2.6mm
U5, U6: AG1171; AG1171_SIL
USB1: TYPE-C_16PIN_2MD_073; Manufacturer Part TYPE-C 16PIN 2MD(073); LCSC C2765186

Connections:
+3.3V: C3.1, C4.1, C5.1, C9.2, C10.2, C11.2, C12.2, Card1.4 (VDD), R1.2, R2.2, R3.1, R11.1, R12.1, R13.1, U1.5 (VOUT), U2.2 (3V3), U4.2 (DVDD), U4.3 (PVDD), U4.17 (AVDD)
+5V: C2.2, C20.1, C21.1, C22.1, C23.1, D1.1 (K), J8.2, U1.1 (VIN), U1.3 (EN), U5.13 (Vpwr), U6.13 (Vpwr)
/I2C_SCL: R12.2, U2.21 (GPIO23), U4.28 (CCLK)
/I2C_SDA: R11.2, U2.20 (GPIO22), U4.27 (CDATA)
/I2S_BCLK: U2.4 (MTMS/GPIO4/ADC1_CH4), U4.5 (SCLK)
/I2S_DIN: U2.7 (MTDO/GPIO7), U4.8 (ASDOUT)
/I2S_DOUT: U2.6 (MTCK/GPIO6/ADC1_CH6), U4.6 (DSDIN)
/I2S_LRCK: U2.5 (MTDI/GPIO5/ADC1_CH5), U4.7 (LRCK)
/I2S_MCLK: U2.8 (GPIO0/ADC1_CH0/XTAL_32K_P), U4.1 (MCLK)
/Line1_F/R: U2.27 (GPIO2/ADC1_CH2), U6.3 (F/R)
/Line1_PD: D4.1 (K), U2.11 (GPIO10)
/Line1_RM: U2.26 (GPIO3/ADC1_CH3), U6.4 (RM)
/Line1_SHK: R18.2, R19.1, U2.9 (GPIO1/ADC1_CH1/XTAL_32K_N)
/Line1_Vin: C16.1, U4.24 (LIN1)
/Line1_Vout: C17.1, U4.12 (LOUT1)
/Line2_F/R: R10.2, U5.3 (F/R)
/Line2_PD: D3.1 (K), R7.2
/Line2_RM: R9.2, U5.4 (RM)
/Line2_SHK: R8.2, R16.2, R17.1
/Line2_Vin: C19.2, U4.22 (LIN2)
/Line2_Vout: C18.2, U4.11 (ROUT1)
/SD_CLK: Card1.5 (CLK(SCLK)), R8.1, U2.17 (GPIO19)
/SD_CS: Card1.2 (CDDAT3(CS)), R7.1, U2.16 (GPIO18)
/SD_MISO: Card1.7 (DAT0(D0)), R10.1, U2.19 (GPIO21)
/SD_MOSI: Card1.3 (CMD(DI)), R9.1, U2.18 (GPIO20)
/usb_D+: U2.14 (GPIO13/USB_D+), U3.6 (I/O1)
/usb_D-: U2.13 (GPIO12/USB_D-), U3.4 (I/O2)
GND: C1.2, C2.1, C3.2, C4.2, C5.2, C6.1, C7.1, C8.1, C9.1, C10.1, C11.1, C12.1, C13.1, C20.2, C21.2, C22.2, C23.2, C24.1, C25.1, Card1.6 (VSS), Card1.10 (GND), Card1.11 (GND), Card1.12 (GND), Card1.13 (GND), D5.2 (A), D6.2 (A), D7.2 (A), D8.2 (A), D13.2 (A), D14.2 (A), J2.2, J3.2, J4.2, J5.3, J8.1, R4.1, R5.1, R6.2, R14.1, R15.2, R16.1, R18.1, U1.2 (GND), U2.1 (GND), U2.28 (GND), U2.29 (GND), U3.2 (GND), U4.4 (DGND), U4.13 (HPGND), U4.18 (AGND), U4.26 (CE), U4.29 (EPAD), U5.12 (GND), U6.12 (GND), USB1.13 (EH), USB1.14 (EH), USB1.A1B12 (GND), USB1.B1A12 (GND)
unnamed: C14.1, J5.2, R14.2
unnamed: C15.1, J5.1, R15.1
unnamed: Card1.8 (DAT1(RSV)), R3.2
unnamed: Card1.1 (DAT2(RSV)), R2.1
unnamed: D1.2 (A), U3.5 (VBUS), USB1.A4B9 (VBUS), USB1.B4A9 (VBUS)
unnamed: D2.2 (A), U2.12 (GPIO11)
unnamed: D2.1 (K), R6.1
unnamed: D3.2 (A), U5.14 (PD)
unnamed: D4.2 (A), U6.14 (PD)
unnamed: D5.1 (K), D9.2 (A), J6.3, U5.2 (Tip)
unnamed: D6.1 (K), D10.2 (A), J6.4, U5.1 (Ring)
unnamed: D9.1 (K), D10.1 (K), D13.1 (K)
unnamed: D7.1 (K), D11.2 (A), J7.3, U6.2 (Tip)
unnamed: D11.1 (K), D12.1 (K), D14.1 (K)
unnamed: D8.1 (K), D12.2 (A), J7.4, U6.1 (Ring)
unnamed: R20.2, R21.1
unnamed: C1.1, R1.1, U2.3 (EN/CHIP_PU)
unnamed: J2.1, U2.15 (GPIO9)
unnamed: J4.1, U2.24 (U0RXD/GPIO17)
unnamed: J3.1, U2.25 (U0TXD/GPIO16)
unnamed: C7.2, U4.19 (ADCVREF)
unnamed: C13.2, R13.2, U4.16 (HPVDD)
unnamed: C15.2, U4.15 (LOUT2)
unnamed: C24.2, U4.23 (RIN1)
unnamed: C25.2, U4.21 (RIN2)
unnamed: C14.2, U4.14 (ROUT2)
unnamed: C8.2, U4.20 (VMID)
unnamed: C6.2, U4.10 (VREF)
unnamed: R17.2, U5.5 (SHK)
unnamed: C19.1, U5.9 (Vin)
unnamed: C18.1, U5.10 (Vout)
unnamed: R19.2, U6.5 (SHK)
unnamed: C16.2, U6.9 (Vin)
unnamed: C17.2, U6.10 (Vout)
unnamed: R4.2, USB1.A5 (CC1)
unnamed: R5.2, USB1.B5 (CC2)
unnamed: U3.1 (I/O1), USB1.A7 (Dn1)
unnamed: U3.3 (I/O2), USB1.A6 (Dp1)

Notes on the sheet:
Caps as close to their respective gnd returns as possible
Pin 1: R Pin 2: L
Boot Jumper
Headphone header for debug
Remove 0R for uSD use
Stuff either Line 2 OR Remove 4x 0R to use uSD
Diode 1N4148 or BAS16
CE Gnd = i2c addr 0x10
Line 2: Right
actual Line1_Vout (post in/out swap) needs to move to Rin2 pre-swap: Line1_Vin move to Rin2 (C25 pad). Relabel as mic! OR Move Line2 mic to Rin1 (C24 pad)
Swapped 2 wires here
Pull up to VCC in SW
I2C pull-ups
Zener BZT03C82 OR P6KE82
Now Line1_Vout (mic)
NC Jtag
Use as UART header or 2x GPIO
ME6211C33M5G-N or AP2112K
Line 2 out is a copy of Line 1
Now Line1_Vin
Line 1: Left
ERROR: D+ / D- swapped on previous board. Need to fix!
Now Line2_Vout (mic)
5V AG1170 needs 3.3V signal to ESP32
In/out are swapped on this board! need to fix in next version!
Now Line2_Vin
